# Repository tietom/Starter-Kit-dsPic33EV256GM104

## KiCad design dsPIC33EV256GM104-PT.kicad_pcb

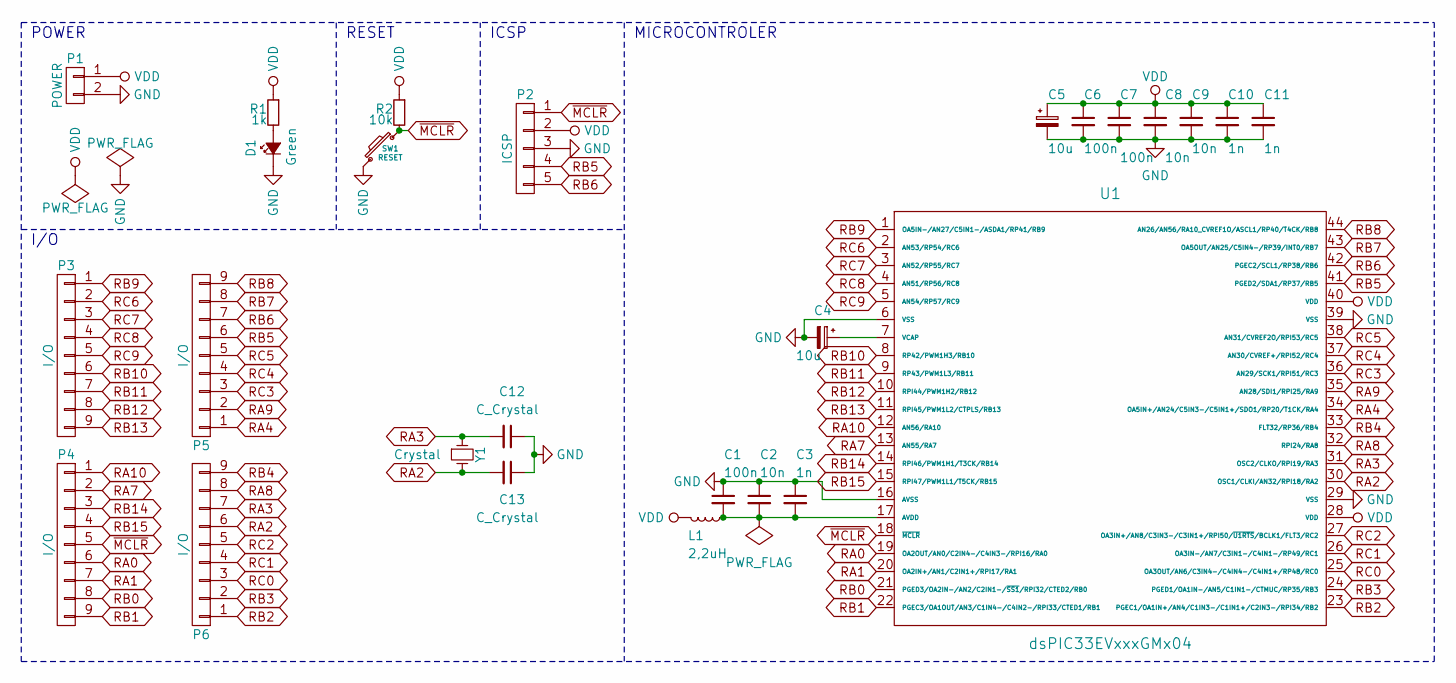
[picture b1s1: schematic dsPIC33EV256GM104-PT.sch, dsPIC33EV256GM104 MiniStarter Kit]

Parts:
C1, C6, C7: 100n; C_0805
C2, C8, C9: 10n; C_0603
C3, C10, C11: 1n; C_0603
C4, C5: 10u; TantalC_SizeC_EIA-6032_Reflow
C12, C13: C_Crystal; C_Disc_D3_P2.5
D1: Green; LED-5MM
L1: 2,2uH; Resistor_SMD+THTuniversal_0805to1206_RM10_HandSoldering
P1: POWER; Pin_Header_Straight_1x02
P2: ICSP; Pin_Header_Straight_1x05
P3, P4, P5, P6: I/O; Pin_Header_Straight_1x09
R1: 1k; R_0805
R2: 10k; R_0805
SW1: RESET; PCB_PUSH
U1: dsPIC33EVxxxGMx04; TQFP-44_10x10mm_Pitch0.8mm
Y1: Crystal; HC-49V

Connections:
GND: C1.1, C2.1, C3.1, C4.2, C5.2, C6.2, C7.2, C8.2, C9.2, C10.2, C11.2, C12.1, C13.1, D1.1 (K), P1.2, P2.3, SW1.2, U1.6 (VSS), U1.16 (AVSS), U1.29 (VSS), U1.39 (VSS)
unnamed: C1.2, C2.2, C3.2, L1.1, U1.17 (AVDD)
unnamed: C4.1, U1.7 (VCAP)
unnamed: D1.2 (A), R1.2
RA0: P4.6, U1.19 (OA2OUT/AN0/C2IN4-/C4IN3-/RPI16/RA0)
RA1: P4.7, U1.20 (OA2IN+/AN1/C2IN1+/RPI17/RA1)
RA2: C13.2, P6.6, U1.30 (OSC1/CLKI/AN32/RPI18/RA2), Y1.2
RA3: C12.2, P6.7, U1.31 (OSC2/CLKO/RPI19/RA3), Y1.1
RA4: P5.1, U1.34 (OA5IN+/AN24/C5IN3-/C5IN1+/SDO1/RP20/T1C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)
RA7: P4.2, U1.13 (AN55/RA7)
RA8: P6.8, U1.32 (RPI24/RA8)
RA9: P5.2, U1.35 (AN28/SDI1/RPI25/RA9)
RA10: P4.1, U1.12 (AN56/RA10)
RB0: P4.8, U1.21 (PGED3/OA2IN-/AN2/C2IN1-/~SS1~/RPI32/CTE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)
RB1: P4.9, U1.22 (PGEC3/OA1OUT/AN3/C1IN4-/C4IN2-/RPI33/CT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)
RB2: P6.1, U1.23 (PGEC1/OA1IN+/AN4/C1IN3-/C1IN1+/C2IN3-/R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)
RB3: P6.2, U1.24 (PGED1/OA1IN-/AN5/C1IN1-/CTMUC/RP35/RB3)
RB4: P6.9, U1.33 (FLT32/RP36/RB4)
RB5: P2.4, P5.6, U1.41 (PGED2/SDA1/RP37/RB5)
RB6: P2.5, P5.7, U1.42 (PGEC2/SCL1/RP38/RB6)
RB7: P5.8, U1.43 (OA5OUT/AN25/C5IN4-/RP39/INT0/RB7)
RB8: P5.9, U1.44 (AN26/AN56/RA10_CVREF1O/ASCL1/RP40/T4CK/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)
RB9: P3.1, U1.1 (OA5IN-/AN27/C5IN1-/ASDA1/RP41/RB9)
RB10: P3.6, U1.8 (RP42/PWM1H3/RB10)
RB11: P3.7, U1.9 (RP43/PWM1L3/RB11)
RB12: P3.8, U1.10 (RPI44/PWM1H2/RB12)
RB13: P3.9, U1.11 (RPI45/PWM1L2/CTPLS/RB13)
RB14: P4.3, U1.14 (RPI46/PWM1H1/T3CK/RB14)
RB15: P4.4, U1.15 (RPI47/PWM1L1/T5CK/RB15)
RC0: P6.3, U1.25 (OA3OUT/AN6/C3IN4-/C4IN4-/C4IN1+/RP48/RC0)
RC1: P6.4, U1.26 (OA3IN-/AN7/C3IN1-/C4IN1-/RP49/RC1)
RC2: P6.5, U1.27 (OA3IN+/AN8/C3IN3-/C3IN1+/RPI50/~U1RTS~/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)
RC3: P5.3, U1.36 (AN29/SCK1/RPI51/RC3)
RC4: P5.4, U1.37 (AN30/CVREF+/RPI52/RC4)
RC5: P5.5, U1.38 (AN31/CVREF2O/RPI53/RC5)
RC6: P3.2, U1.2 (AN53/RP54/RC6)
RC7: P3.3, U1.3 (AN52/RP55/RC7)
RC8: P3.4, U1.4 (AN51/RP56/RC8)
RC9: P3.5, U1.5 (AN54/RP57/RC9)
VDD: C5.1, C6.1, C7.1, C8.1, C9.1, C10.1, C11.1, L1.2, P1.1, P2.2, R1.1, R2.1, U1.28 (VDD), U1.40 (VDD)
~MCLR~: P2.1, P4.5, R2.2, SW1.1, U1.18 (~MCLR~)

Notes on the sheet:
POWER
RESET
ICSP
MICROCONTROLER
I/O

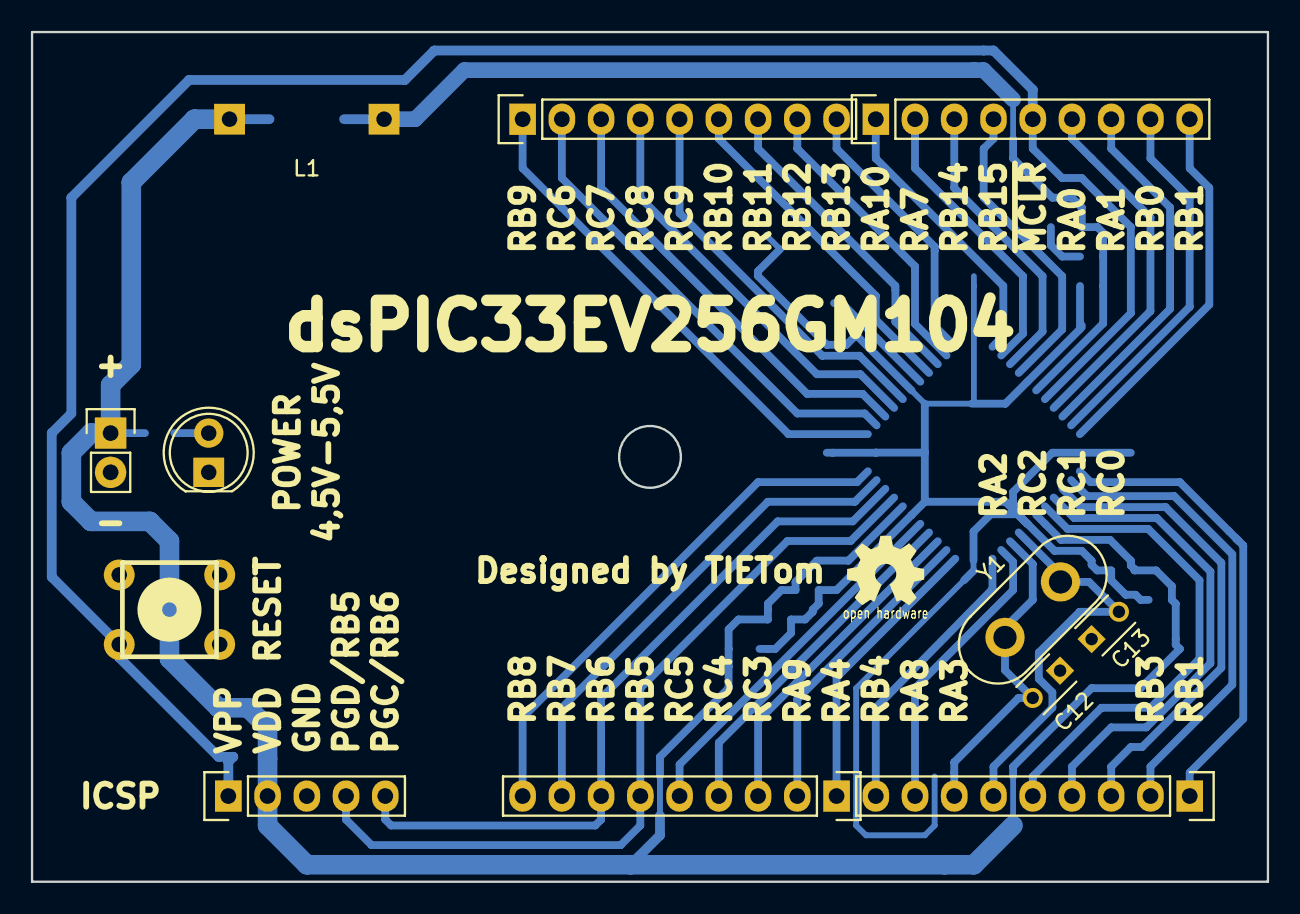
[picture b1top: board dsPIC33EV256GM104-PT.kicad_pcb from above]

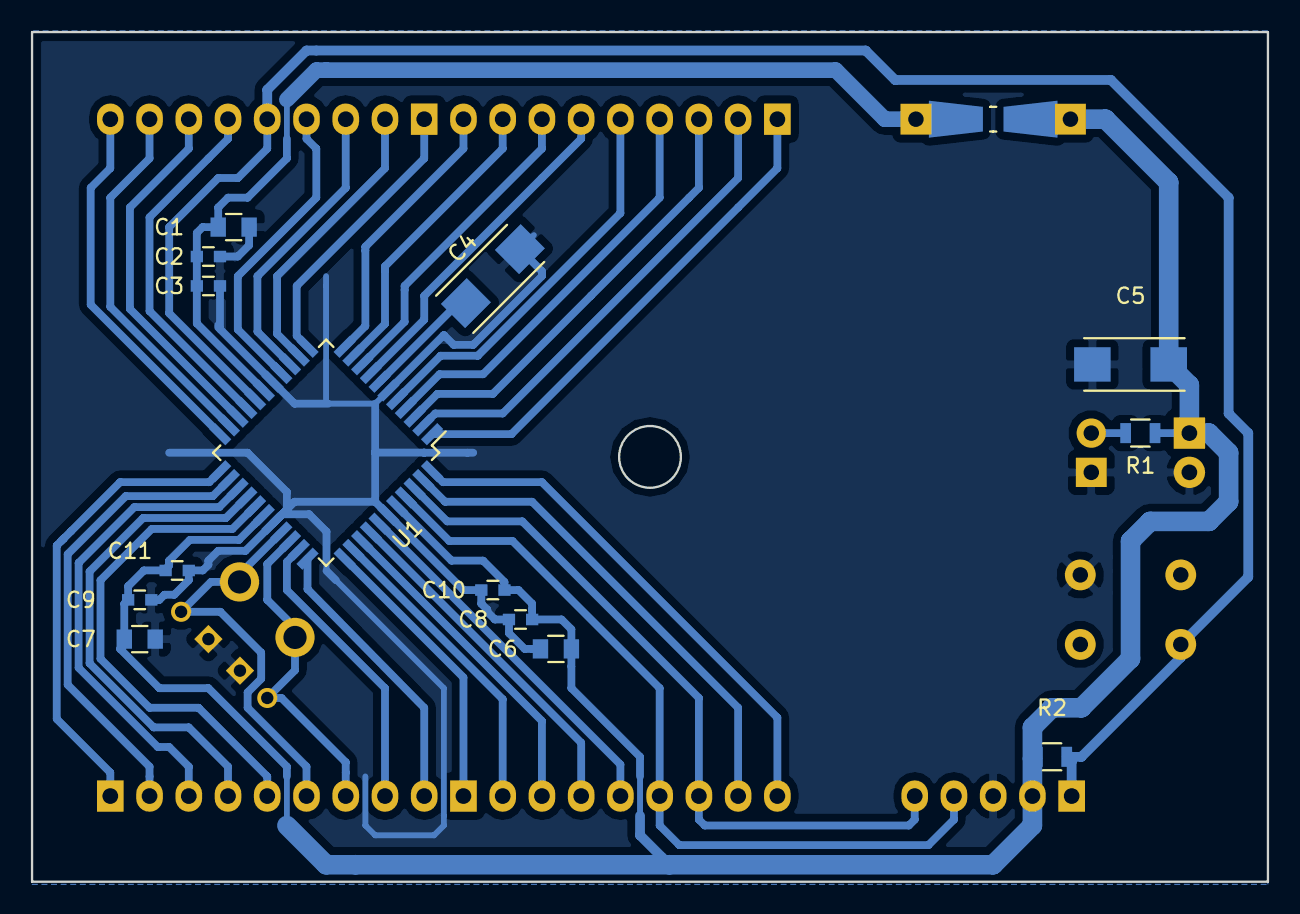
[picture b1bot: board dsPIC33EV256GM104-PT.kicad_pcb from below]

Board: 2 copper layers, 80.0 x 55.0 mm, 26 parts (15 on the bottom side), 41 nets.

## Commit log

2015-12-04 Starter Kit for dsPIC33EV256GM104
    Small starter Kit for dsPIC33EV256GM104 created in KiCad for Z23A case
